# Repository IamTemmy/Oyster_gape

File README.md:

# Oyster_gape

Non-contact measurement of oyster valve **gape** (how far the shells open and
close) using a Micronas **HAL 2425** Hall-effect sensor on one shell and a small
magnet on the other. As the gap changes, the sensor output changes. This repo
covers the sensor engineering: characterizing and **linearizing** the HAL 2425 so
its output reads linearly in millimetres, then a **three-sensor bench system**
(Board B) that shows live gape on a web dashboard, with a **per-unit tare** so
each unit reports true gape from its own closed baseline.

This is a clean restart. Nothing here is inherited unverified from prior work —
every constant is measured and documented.

---

## Demo

Three clothespin "oysters" on Board B's live dashboard — each shell opens in
proportion to the measured gape. Closed reads 0.00 mm (per-unit tare); the
slightest press registers immediately.
**[Watch the full video →](https://github.com/IamTemmy/Oyster_gape/releases/tag/v0.1-bench-demo)**
· more in [`docs/demo.md`](docs/demo.md).

---

## Current stage

**Bench system working — 25 mT + tare (Board B).** The full method is proven on
three clothespin "oysters" (pegs standing in for real animals):

- Sensors characterized and **linearized** (Micronas workflow, Procedure 03),
  first at 12 mT then re-done at **25 mT** (window 8.0–20.0) so the closed peg sits
  on the active ramp instead of in the dead zone.
- **Board B** (ESP32-WROVER) reads all three sensors (S1/S2/S3 → GPIO34/35/32, all
  ADC1) and serves a live **web dashboard** (`firmware/06_board_b_tare`).
- **Per-unit tare:** each unit records its own closed reading as a baseline and
  reports **true gape from closed** — `gape = (mV − baseline) / m`. The intercept
  cancels in that subtraction, so the per-unit mounting offset drops out. This is
  what lets one lab calibration serve many differently-mounted animals.

Per-sensor lines and the full method:
[`data/analysis/deployment_calibration.md`](data/analysis/deployment_calibration.md).
Watch it work: [demo](docs/demo.md).

**Next (deployment):** re-run the same method at the range chosen for real oysters
(see decisions log), add a mounting jig for consistent closed standoff, and
flash-persist the baselines so a tare survives power cycles.

---

## Hardware facts (current rig)

| Item | Value |
|------|-------|
| Sensor | Micronas HAL 2425 (16 linearization setpoints) |
| Programmer / software | HAL-APB on COM-port, HAL/HAR 24xy Programming Environment (SW v3.04) |
| Controller | ESP32-WROVER (Freenove) |
| Driver | Geckodrive G251 — **fixed 10 microsteps/full step → 2000 pulses/rev** |
| Motor | 200 full-step |
| Magnet | 3/8" dia × 1/8" thick, N40 neodymium, axially magnetized |

### Pin map

| Signal | ESP32 | Notes |
|--------|-------|-------|
| STEP | GPIO18 | → G251 Terminal 10 |
| DIR  | GPIO19 | → G251 Terminal 9 |
| Sensor analog in | GPIO34 | ADC1_CH6, input-only. **Not** GPIO4 (that is ADC2, WiFi-conflicting) |
| Common ground | GND | shared with G251 Terminal 12 |

### Analog front end (sensor output → ESP32) — DECIDED: ÷1.5, no cap

- **Divider: ÷1.5** (two 10 kΩ in parallel = 5 kΩ on top, one 10 kΩ to ground).
  The Stage 02 2×2 test showed ÷1.5 and ÷2 back-scale to the same true curve
  within 0.3% — ÷1.5 does **not** clip with this magnet/geometry — while ÷1.5
  spans ~1.33× more mV at the pin, giving more ADC resolution. (Re-check if a
  future geometry brings the magnet much closer and raises the output.)
- **No filter cap.** No-cap noise is ~6 mV SD → ~0.45 mV after 200-sample
  averaging — already excellent. On this ÷1.5 setup the cap **reproducibly
  raised** noise (~21 mV SD, confirmed on a clean retest — not a loose
  connection). Cause not pinned down (likely the specific cap interacting with
  the breadboard/ADC), but irrelevant: the cap isn't needed and hurts here, so
  it's dropped. See data/analysis/.
- Decouple the sensor's 5 V supply with 100 nF + ~4.7 µF at its pins
  (output is ratiometric, so supply ripple = error).

---

## Key decisions log

- **Noise:** keep the ESP32 (per advisor); attack noise in firmware via
  oversampling + averaging + settle time, on ADC1. External ADC (e.g. ADS1115)
  held as a fallback only.
- **Analog front end:** **÷1.5 divider, no cap** (Stage 02 2×2 test). ÷1.5
  proven not to clip (back-scales to ÷2 within 0.3%) and gives more resolution;
  cap unneeded because 200-sample averaging drives noise to ~0.5 mV.
- **Magnetic range:** ±3 mT is **blind below ~12 mm** with this magnet (near field
  clips); higher ranges reach smaller gaps. **Bench: ±25 mT** — chosen and
  bench-proven (window 8.0–20.0) because it places the peg's closed gap on the ramp
  without pushing the window start into the steep shoulder (the F:000000 spike).
  **Deployment: likely ±3 mT** for real (larger) oysters — the professor's lean,
  for its longer operating range at larger separations. The *method* is
  range-independent (linearize → mount so closed is on-ramp → tare), so deployment
  re-runs it at the final range once the oyster geometry is known.
  *(Updated 2026-07-05; earlier this read "final choice pending the measured gape window.")*
- **Distance constant:** measured = **0.001 mm/pulse** (1000 pulses/mm,
  2.0 mm/rev), Procedure 01.
- **Output polarity:** sensor output **falls** with increasing gap
  (closed = high mV ~3.6 V, open = low mV). Kept on purpose: it places the
  closed→just-opening transition in the high-signal, high-resolution region —
  the event the research most cares about. A falling curve linearizes exactly
  like a rising one. Deployment caveat: "fully open" and "unpowered / broken
  wire" both read low — rely on the HAL's wire-break detection to disambiguate.
- **Per-sensor calibration:** every sensor is characterized and linearized
  **individually** — setpoint files are NOT shareable between units (intrinsic
  part spread + mounting variation from bent pins + magnet pairing). The process
  is identical each time and the high-level settings (range, output mapping) are
  shared; only the sweep + setpoints + a per-unit 2-point calibration are
  repeated. The 2-point cal is what absorbs mounting-distance variation. A sensor
  must be characterized in (or in a jig replicating) its final mounting geometry.
  Future shortcut to validate empirically: if several sensors' curve *shapes*
  match, share one curve + per-unit 2-point cal only.
- **LOCK is irreversible.** Locking a sensor can never be undone — every
  programming session ends with an explicit LOCK checklist before that button.

---

## Conventions

- One firmware sketch per folder (Arduino requirement), numbered by stage.
- Every stage has a matching `docs/procedures/NN_*.md` with a results table
  filled in from the real run.
- Raw data lands in `data/` with the sketch/run that produced it named in the file.

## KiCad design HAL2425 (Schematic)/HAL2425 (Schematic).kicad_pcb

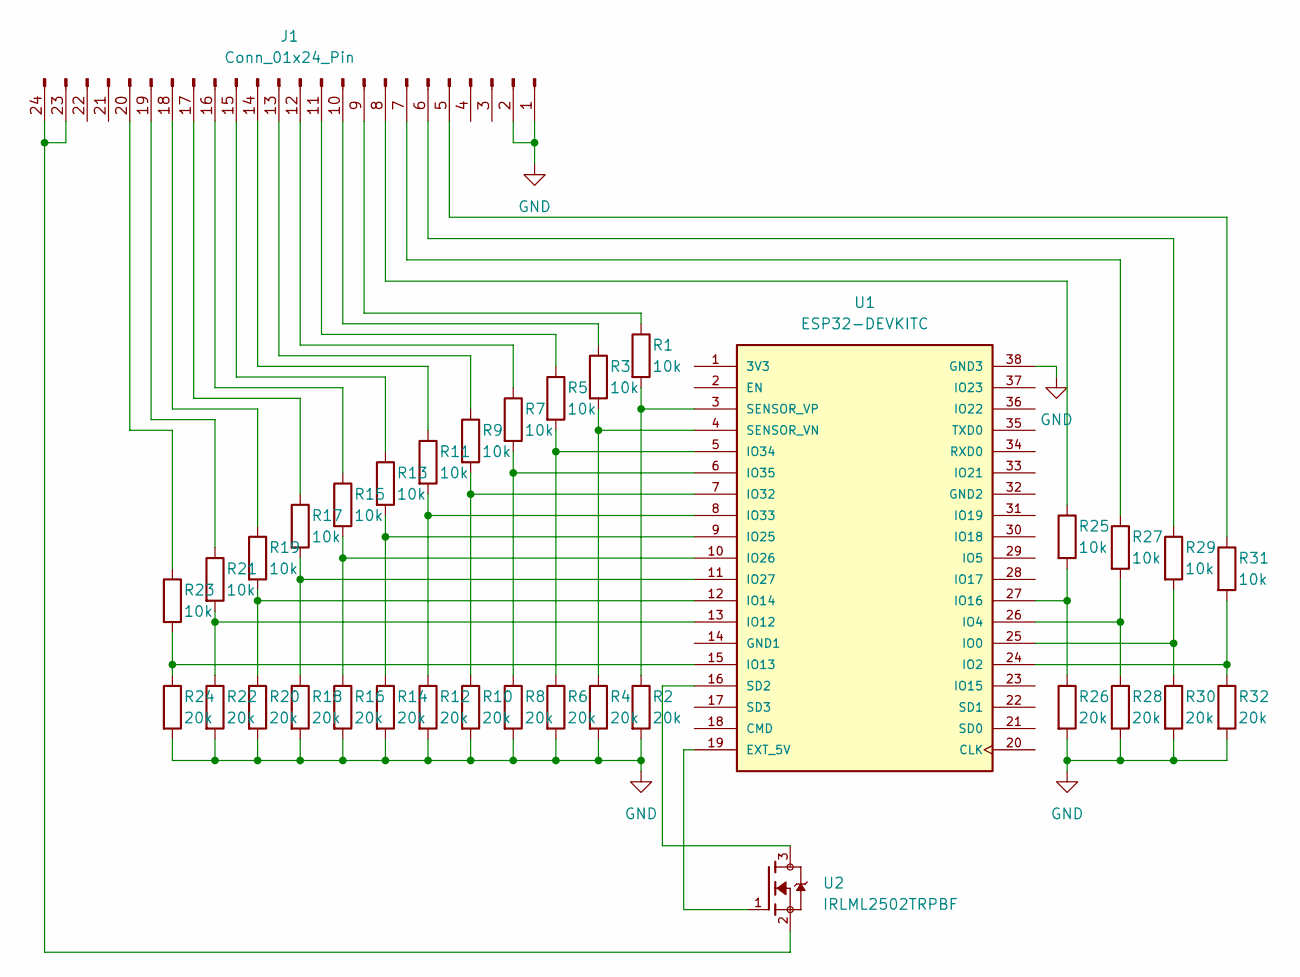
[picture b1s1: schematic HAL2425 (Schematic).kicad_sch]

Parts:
J1: Conn_01x24_Pin; PinHeader_1x24_P2.54mm_Vertical
R1, R3, R5, R7, R9, R11, R13, R15, R17, R19, R21, R23, R25, R27, R29, R31: 10k; R_1206_3216Metric_Pad1.30x1.75mm_HandSolder
R2, R4, R6, R8, R10, R12, R14, R16, R18, R20, R22, R24, R26, R28, R30, R32: 20k; R_1206_3216Metric_Pad1.30x1.75mm_HandSolder
U1: ESP32-DEVKITC; MODULE_ESP32-DEVKITC; PARTREV N/A
U2: IRLML2502TRPBF; SOT23

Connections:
GND: J1.1, J1.2, R2.2, R4.2, R6.2, R8.2, R10.2, R12.2, R14.2, R16.2, R18.2, R20.2, R22.2, R24.2, R26.2, R28.2, R30.2, R32.2, U1.38 (GND3)
unnamed: J1.5, R31.1
unnamed: J1.6, R29.1
unnamed: J1.7, R27.1
unnamed: J1.8, R25.1
unnamed: J1.9, R1.1
unnamed: J1.10, R3.1
unnamed: J1.11, R5.1
unnamed: J1.12, R7.1
unnamed: J1.13, R9.1
unnamed: J1.14, R11.1
unnamed: J1.15, R13.1
unnamed: J1.16, R15.1
unnamed: J1.17, R17.1
unnamed: J1.18, R19.1
unnamed: J1.19, R21.1
unnamed: J1.20, R23.1
unnamed 17: J1.23, J1.24, U2.2; also elsewhere on the board
unnamed 18: U1.19 (EXT_5V), U2.1; also elsewhere on the board
unnamed: R29.2, R30.1, U1.25 (IO0)
unnamed: R31.2, R32.1, U1.24 (IO2)
unnamed: R27.2, R28.1, U1.26 (IO4)
unnamed: R21.2, R22.1, U1.13 (IO12)
unnamed: R23.2, R24.1, U1.15 (IO13)
unnamed: R19.2, R20.1, U1.12 (IO14)
unnamed: R25.2, R26.1, U1.27 (IO16)
unnamed: R13.2, R14.1, U1.9 (IO25)
unnamed: R15.2, R16.1, U1.10 (IO26)
unnamed: R17.2, R18.1, U1.11 (IO27)
unnamed: R9.2, R10.1, U1.7 (IO32)
unnamed: R11.2, R12.1, U1.8 (IO33)
unnamed: R5.2, R6.1, U1.5 (IO34)
unnamed: R7.2, R8.1, U1.6 (IO35)
unnamed 33: U1.16 (SD2), U2.3; also elsewhere on the board
unnamed: R3.2, R4.1, U1.4 (SENSOR_VN)
unnamed: R1.2, R2.1, U1.3 (SENSOR_VP)

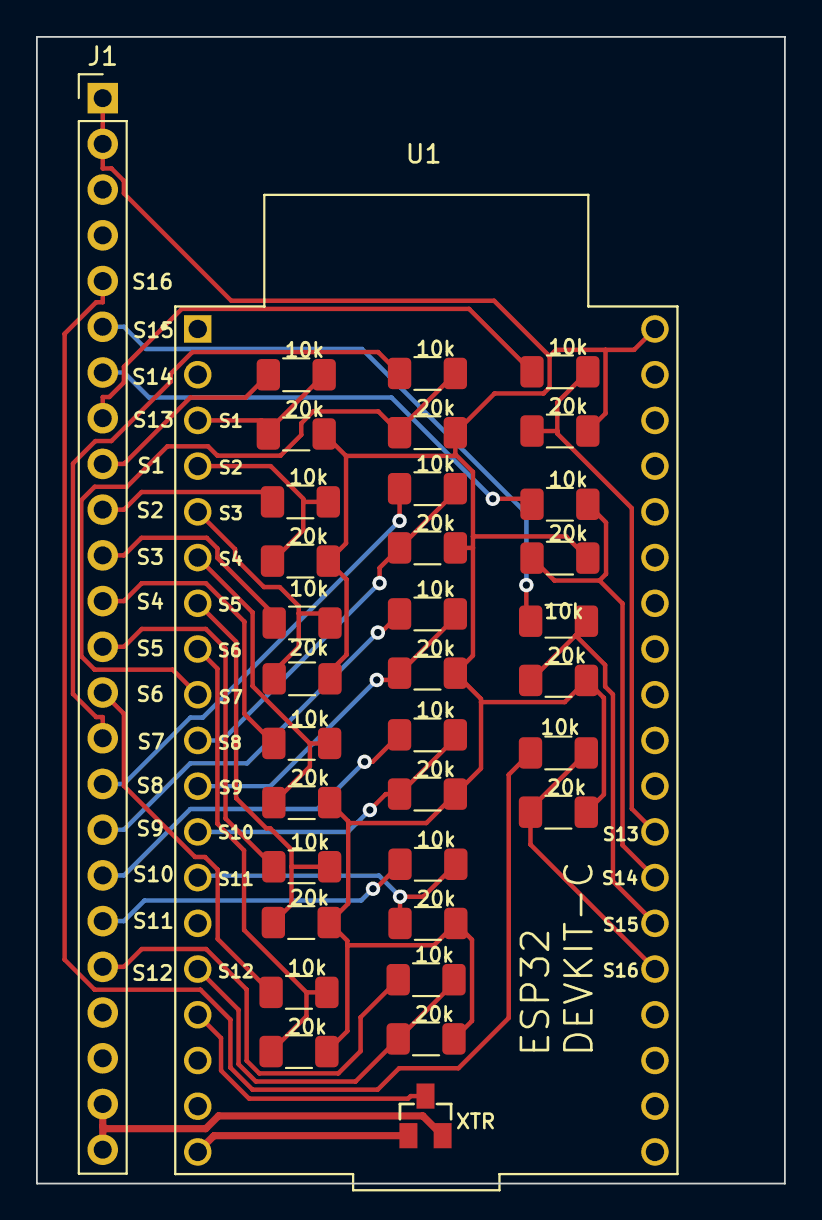
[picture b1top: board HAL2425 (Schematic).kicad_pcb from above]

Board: 2 copper layers, 41.6 x 63.7 mm, 35 parts (0 on the bottom side), 36 nets.

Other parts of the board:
XTR: IRLML2502TRPBF; SOT23

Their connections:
unnamed 17: XTR.2; also elsewhere on the board
unnamed 18: XTR.1; also elsewhere on the board
unnamed 33: XTR.3; also elsewhere on the board

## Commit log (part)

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2024-02-22 Updated to print in .csv format
2024-03-06 Added 5 readings with average and standard deviation
    This change prints the readings in sets of 5, 10 ms apart as well as the average and standard deviations of those readings. The Statistical library needs to be installed for the Arduino IDE.
2024-03-07 Changed csv title for readings to match readingSetSize
2024-08-22 Added mbrace aws
    These files are sketches and a header file for connecting devices to AWS IoT Core
2026-06-13 Stage 01: leadscrew calibration sketch, procedure, and README
2026-06-13 Set DIR_AWAY_LEVEL to LOW (positive jog now moves away from sensor)
2026-06-13 Record leadscrew calibration results: 0.001 mm/pulse (2.0 mm/rev)
2026-06-13 Stage 02: add host logger + procedure; finalize sweep sketch
2026-06-13 Document output polarity and per-sensor calibration policy
2026-06-14 Stage 02: front end decided — div1.5, no cap (cap reproducibly adds noise); add data + figures
2026-06-14 Stage 02: eight-range characterization sweeps + family and sensitivity figures
2026-06-14 Stage 03: three-mode linearization sketch + procedure
2026-06-15 Stage 03: 100mT linearized + verified (2.6%); 200/400mT documented impractical
2026-06-15 Stage 03 complete: 6 ranges linearized + verified (1.4-3.1%); range ladder + findings
2026-06-15 Stage 03: add before/after + coverage figures for review
